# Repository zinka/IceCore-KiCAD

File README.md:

# IceCore-KiCAD
A KiCAD version of IceCore (https://github.com/folknology/IceCore) Lattice FPGA board

**Top View**

**Bottom View**

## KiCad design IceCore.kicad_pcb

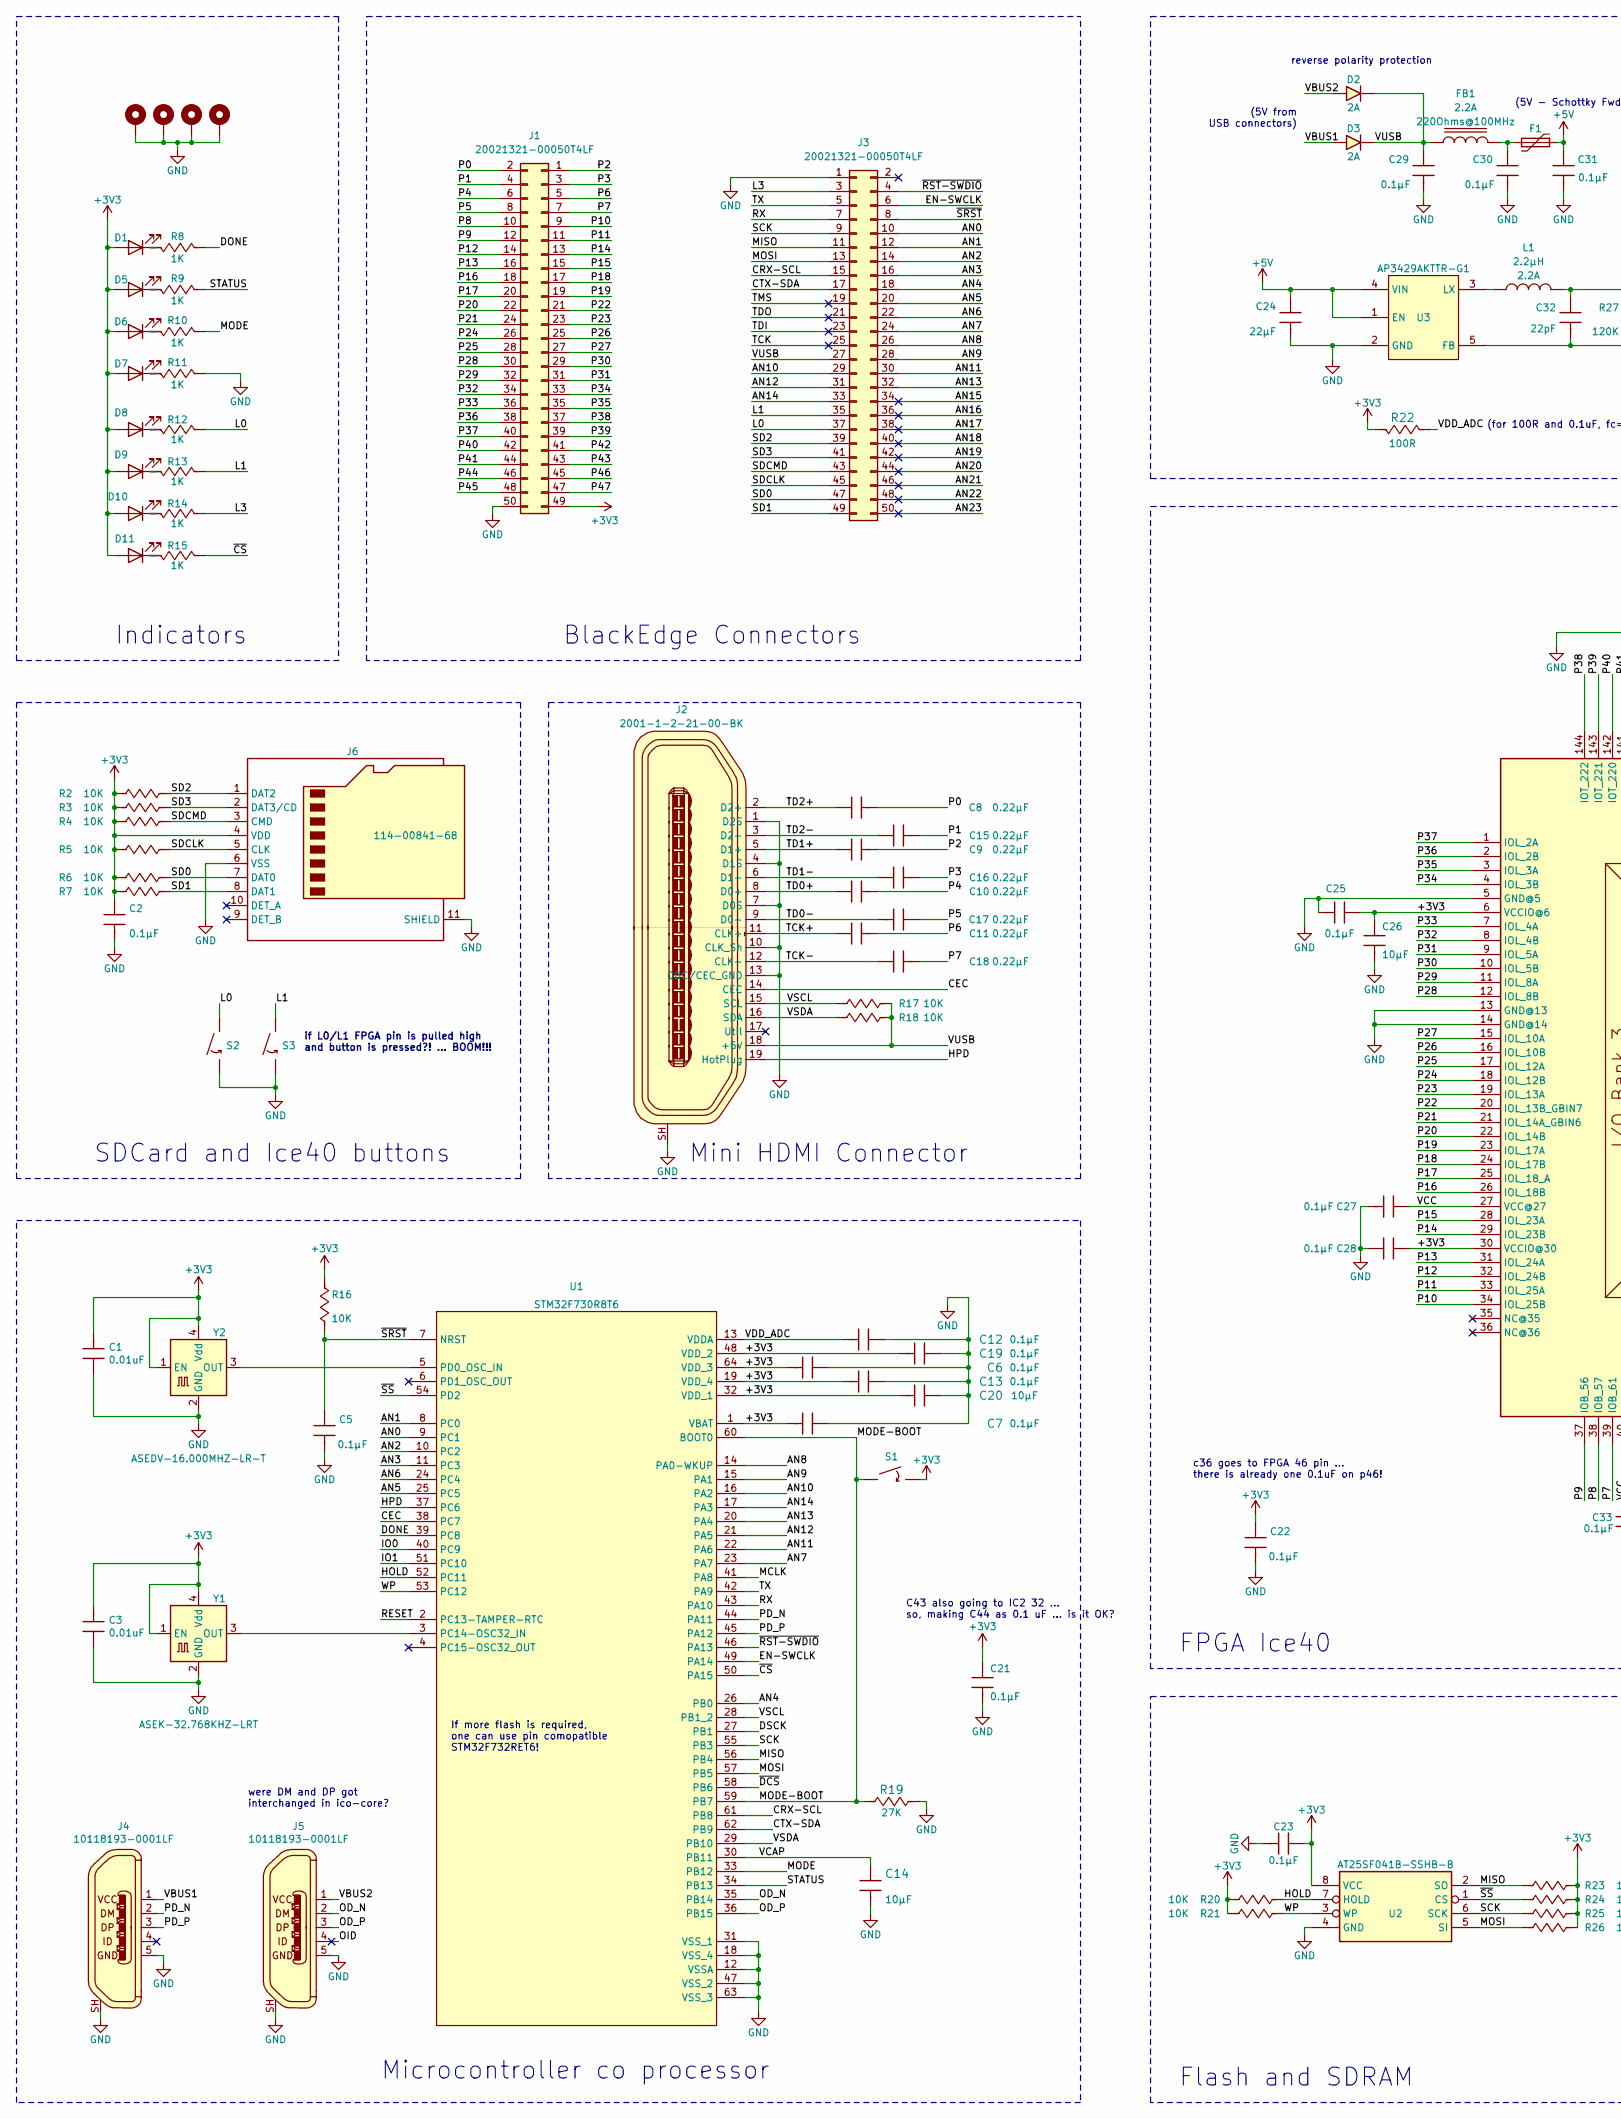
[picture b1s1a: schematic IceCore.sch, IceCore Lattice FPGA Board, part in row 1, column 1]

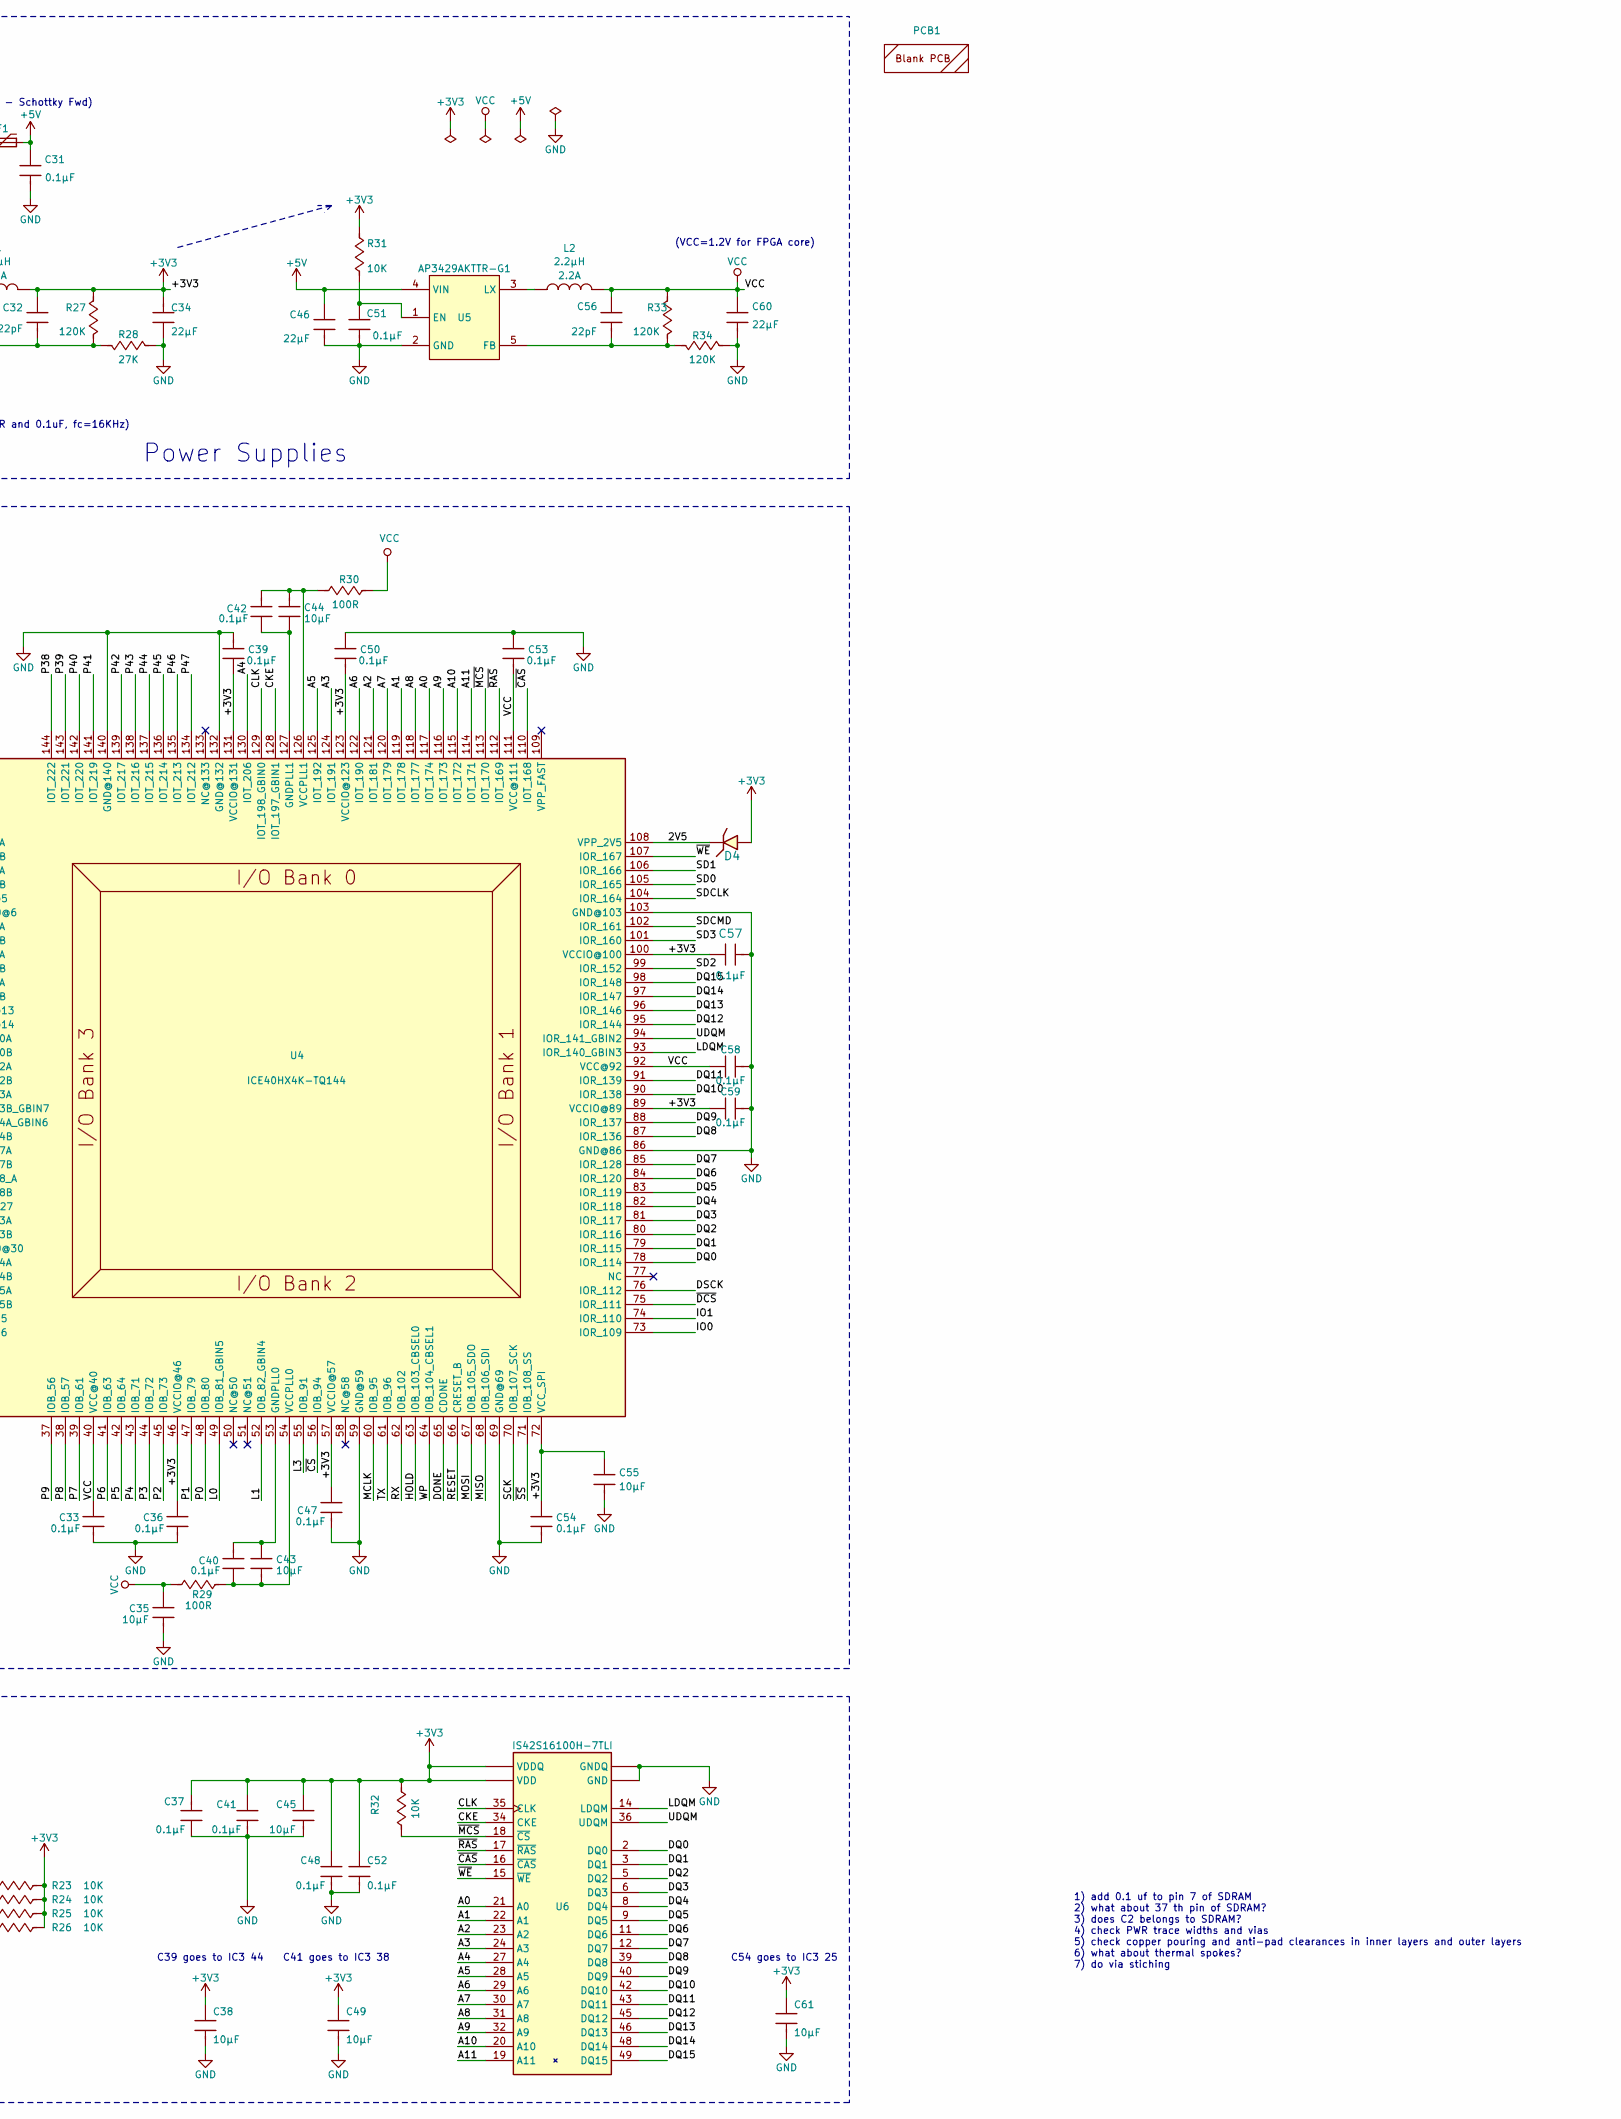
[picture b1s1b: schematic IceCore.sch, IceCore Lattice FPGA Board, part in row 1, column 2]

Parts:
C1, C3: CAP-000017-00; C_0402_1005Metric; Tolerance (%) ±10%; Rated Voltage (Volt) 50V; Manufacturer Part Number GCM155R71H103KA55D
C2, C5, C6, C7, C12, C13, C19, C21, C22, C23, C25, C27, C28, C29, C30, C31, C33, C36, C37, C39, C40, C41, C42, C47, C48, C50, C51, C52, C53, C54, C57, C58, C59: CAP-000004-00; C_0402_1005Metric; Tolerance (%) ±10%; Voltage Rated (Volt) 16V; Manufacturer Part Number GRM155R71C104KA88D
C8, C9, C10, C11, C15, C16, C17, C18: CAP-000182-00; C_0402_1005Metric; Rated Voltage (Volt) 16V; Tolerance (%) ±10%; Manufacturer Part Number GRM155R71C224KA12D
C14, C20, C35, C43, C44, C45: CAP-000178-00; C_0603_1608Metric; Rated Voltage (Volt) 16V; Tolerance (%) ±20%; Manufacturer Part Number CL10X106MO8NRNC
C24, C34, C46, C60: CAP-000164-00; C_0805_2012Metric; Rated Voltage (Volt) 10V; Tolerance (%) ±20%; Manufacturer Part Number GRM21BC81A226ME44L
C26, C38, C49, C55, C61: CAP-000178-00; C_0603_1608Metric; Tolerance (%) ±20%; Rated Voltage (Volt) 16V; Manufacturer Part Number CL10X106MO8NRNC
C32, C56: CAP-000168-00; C_0402_1005Metric; Rated Voltage (Volt) 50V; Tolerance (%) ±5%; Manufacturer Part Number GCM1555C1H220JA16D
D1, D5, D6, D7, D8, D9, D10, D11: DIO-000055-00; LED_0603_1608Metric; Forward Voltage (Volt) 2V; Manufacturer Part Number APT1608EC
D2, D3: DIO-000179-00; D_SOD-123F; Forward Voltage (Volt) 550mV@2A; Rated Voltage (Volt) 40V; Manufacturer Part Number SS24FL
D4: DIO-000186-00; D_SOD-323; Forward Voltage (Volt) 1V@15mA; Rated Voltage (Volt) 70V; Manufacturer Part Number BAS70JFILM
F1: PRO-000190-00; Fuse_1210_3225Metric; Manufacturer Part Number 0ZCH0075AF2E
FB1: IND-000180-00; L_0603_1608Metric; Current Rating (Ampere) 2.2A; Manufacturer Part Number BLM18KG221SN1D
H1, H2, H3, H4: MountingHole_Pad; 2.5MM-HOLE
J1, J3: CON-000177-00; PinSocket_2x25_P1.27mm_Vertical_SMD; Manufacturer Part Number 20021321-00050T4LF
J2: CON-000176-00; HDMI_Mini_Female_2001-1-2-21-00-BK; Manufacturer Part Number 2001-1-2-21-00-BK
J4, J5: CON-000183-00; USB_Micro_B_Female_10118193-0001LF; Manufacturer Part Number 10118193-0001LF
J6: CON-000174-00; AMPHENOL_1140084168; Manufacturer Part Number 114-00841-68
L1, L2: IND-000181-00; L_Taiyo-Yuden_NR-40xx; Current Rating (Ampere) 2.2A; Manufacturer Part Number NRS4018T2R2MDGJ
PCB1: BlankPCB
R2, R3, R4, R5, R6, R7, R16, R17, R18, R20, R21, R23, R24, R25, R26, R31, R32: RES-000076-00; R_0402_1005Metric; Tolerance (%) ±1%; Manufacturer Part Number RC0402FR-1310KL
R8, R9, R10, R11, R12, R13, R14, R15: RES-000092-00; R_0402_1005Metric; Tolerance (%) ±1%; Manufacturer Part Number RC0402FR-071KL
R19, R28: RES-000167-00; R_0402_1005Metric; Tolerance (%) ±1%; Manufacturer Part Number RC0402FR-0727KL
R22, R29, R30: RES-000074-00; R_0402_1005Metric; Tolerance (%) ±1%; Manufacturer Part Number RC0402FR-07100RL
R27, R33, R34: RES-000166-00; R_0402_1005Metric; Tolerance (%) ±1%; Manufacturer Part Number RC0402FR-07120KL
S1, S2, S3: MEC-000189-00; PTS636SL43SMTRLFS; Manufacturer Part Number PTS636 SL43 SMTR LFS
U1: ICS-000169-00; LQFP-64_10x10mm_P0.5mm; Manufacturer Part Number STM32F730R8T6
U2: ICS-000173-00; SOIC-8_3.9x4.9mm_P1.27mm; Manufacturer Part Number AT25SF041B-SSHB-B
U3, U5: PWR-000165-00; TSOT-23-5; Manufacturer Part Number AP3429AKTTR-G1
U4: ICS-000170-00; TQFP-144_20x20mm_P0.5mm; Manufacturer Part Number ICE40HX4K-TQ144
U6: ICS-000172-00; TSOP-2-50; Manufacturer Part Number IS42S16100H-7TLI
Y1: CLK-000184-00; Oscillator_SMD_Abracon_ASE-4Pin_3.2x2.5mm; Manufacturer Part Number ASEK-32.768KHZ-LRT
Y2: CLK-000185-00; Oscillator_SMD_Abracon_ASE-4Pin_3.2x2.5mm; Manufacturer Part Number ASEDV-16.000MHZ-LR-T

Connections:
+3V3: C1.2, C2.1, C3.2, C6.2, C7.2, C13.2, C19.2, C20.2, C21.1, C22.1, C23.1, C25.1, C26.1, C28.2, C32.1, C34.2, C36.1, C37.2, C38.1, C39.1, C41.1, C45.1, C47.1, C48.1, C49.1, C50.2, C52.1, C54.1, C55.1, C57.1, C59.1, C61.1, D1.2 (A), D4.2 (Anode), D5.2 (A), D6.2 (A), D7.2 (A), D8.2 (A), D9.2 (A), D10.2 (A), D11.2 (A), J1.49, J6.4 (VDD), L1.2, R2.2, R3.2, R4.2, R5.2, R6.2, R7.2, R16.2, R20.1, R21.1, R22.1, R23.1, R24.1, R25.1, R26.1, R27.2, R31.1, R32.2, S1.2, U1.1 (VBAT), U1.19 (VDD_4), U1.32 (VDD_1), U1.48 (VDD_2), U1.64 (VDD_3), U2.8 (VCC), U4.6 (VCCIO@6), U4.30 (VCCIO@30), U4.46 (VCCIO@46), U4.57 (VCCIO@57), U4.72 (VCC_SPI), U4.89 (VCCIO@89), U4.100 (VCCIO@100), U4.123 (VCCIO@123), U4.131 (VCCIO@131), U6.1 (VDD), U6.7 (VDDQ), U6.13 (VDDQ), U6.25 (VDD), U6.38 (VDDQ), U6.44 (VDDQ), Y1.1 (EN), Y1.4 (Vdd), Y2.1 (EN), Y2.4 (Vdd)
+5V: C24.1, C31.1, C46.1, F1.1, U3.1 (EN), U3.4 (VIN), U5.4 (VIN)
/2V5: D4.1 (Cathode), U4.108 (VPP_2V5)
/A0: U4.117 (IOT_174), U6.21 (A0)
/A1: U4.119 (IOT_178), U6.22 (A1)
/A2: U4.121 (IOT_181), U6.23 (A2)
/A3: U4.124 (IOT_191), U6.24 (A3)
/A4: U4.130 (IOT_206), U6.27 (A4)
/A5: U4.125 (IOT_192), U6.28 (A5)
/A6: U4.122 (IOT_190), U6.29 (A6)
/A7: U4.120 (IOT_179), U6.30 (A7)
/A8: U4.118 (IOT_177), U6.31 (A8)
/A9: U4.116 (IOT_173), U6.32 (A9)
/A10: U4.115 (IOT_172), U6.20 (A10)
/A11: U4.114 (IOT_171), U6.19 (A11)
/AN0: J3.10, U1.9 (PC1)
/AN1: J3.12, U1.8 (PC0)
/AN2: J3.14, U1.10 (PC2)
/AN3: J3.16, U1.11 (PC3)
/AN4: J3.18, U1.26 (PB0)
/AN5: J3.20, U1.25 (PC5)
/AN6: J3.22, U1.24 (PC4)
/AN7: J3.24, U1.23 (PA7)
/AN8: J3.26, U1.14 (PA0-WKUP)
/AN9: J3.28, U1.15 (PA1)
/AN10: J3.29, U1.16 (PA2)
/AN11: J3.30, U1.22 (PA6)
/AN12: J3.31, U1.21 (PA5)
/AN13: J3.32, U1.20 (PA4)
/AN14: J3.33, U1.17 (PA3)
/AN15: J3.34
/AN16: J3.36
/AN17: J3.38
/AN18: J3.40
/AN19: J3.42
/AN20: J3.44
/AN21: J3.46
/AN22: J3.48
/AN23: J3.50
/CEC: J2.14 (CEC), U1.38 (PC7)
/CKE: U4.128 (IOT_197_GBIN1), U6.34 (CKE)
/CLK: U4.129 (IOT_198_GBIN0), U6.35 (CLK)
/CRX-SCL: J3.15, U1.61 (PB8)
/CTX-SDA: J3.17, U1.62 (PB9)
/DONE: R8.1, U1.39 (PC8), U4.65 (CDONE)
/DQ0: U4.78 (IOR_114), U6.2 (DQ0)
/DQ1: U4.79 (IOR_115), U6.3 (DQ1)
/DQ2: U4.80 (IOR_116), U6.5 (DQ2)
/DQ3: U4.81 (IOR_117), U6.6 (DQ3)
/DQ4: U4.82 (IOR_118), U6.8 (DQ4)
/DQ5: U4.83 (IOR_119), U6.9 (DQ5)
/DQ6: U4.84 (IOR_120), U6.11 (DQ6)
/DQ7: U4.85 (IOR_128), U6.12 (DQ7)
/DQ8: U4.87 (IOR_136), U6.39 (DQ8)
/DQ9: U4.88 (IOR_137), U6.40 (DQ9)
/DQ10: U4.90 (IOR_138), U6.42 (DQ10)
/DQ11: U4.91 (IOR_139), U6.43 (DQ11)
/DQ12: U4.95 (IOR_144), U6.45 (DQ12)
/DQ13: U4.96 (IOR_146), U6.46 (DQ13)
/DQ14: U4.97 (IOR_147), U6.48 (DQ14)
/DQ15: U4.98 (IOR_148), U6.49 (DQ15)
/DSCK: U1.27 (PB1), U4.76 (IOR_112)
/EN-SWCLK: J3.6, U1.49 (PA14)
/HOLD: R20.2, U1.52 (PC11), U2.7 (HOLD), U4.63 (IOB_103_CBSEL0)
/HPD: J2.19 (HotPlug), U1.37 (PC6)
/IO0: U1.40 (PC9), U4.73 (IOR_109)
/IO1: U1.51 (PC10), U4.74 (IOR_110)
/L0: J3.37, R12.2, S2.1, U4.49 (IOB_81_GBIN5)
/L1: J3.35, R13.2, S3.1, U4.52 (IOB_82_GBIN4)
/L3: J3.3, R14.2, U4.55 (IOB_91)
/LDQM: U4.93 (IOR_140_GBIN3), U6.14 (LDQM)
/MCLK: U1.41 (PA8), U4.60 (IOB_95)
/MISO: J3.11, R23.2, U1.56 (PB4), U2.2 (SO), U4.68 (IOB_106_SDI)
/MODE: R10.1, U1.33 (PB12)
/MODE-BOOT: R19.1, S1.1, U1.59 (PB7), U1.60 (BOOT0)
/MOSI: J3.13, R26.2, U1.57 (PB5), U2.5 (SI), U4.67 (IOB_105_SDO)
/OD_N: J5.2, U1.35 (PB14)
/OD_P: J5.3, U1.36 (PB15)
/OID: J5.4
/P0: C8.2, J1.2, U4.48 (IOB_80)
/P1: C15.2, J1.4, U4.47 (IOB_79)
/P2: C9.2, J1.1, U4.45 (IOB_73)
/P3: C16.2, J1.3, U4.44 (IOB_72)
/P4: C10.2, J1.6, U4.43 (IOB_71)
/P5: C17.1, J1.8, U4.42 (IOB_64)
/P6: C11.2, J1.5, U4.41 (IOB_63)
/P7: C18.2, J1.7, U4.39 (IOB_61)
/P8: J1.10, U4.38 (IOB_57)
/P9: J1.12, U4.37 (IOB_56)
/P10: J1.9, U4.34 (IOL_25B)
/P11: J1.11, U4.33 (IOL_25A)
/P12: J1.14, U4.32 (IOL_24B)
/P13: J1.16, U4.31 (IOL_24A)
/P14: J1.13, U4.29 (IOL_23B)
/P15: J1.15, U4.28 (IOL_23A)
/P16: J1.18, U4.26 (IOL_18B)
/P17: J1.20, U4.25 (IOL_18_A)
/P18: J1.17, U4.24 (IOL_17B)
/P19: J1.19, U4.23 (IOL_17A)
/P20: J1.22, U4.22 (IOL_14B)
/P21: J1.24, U4.21 (IOL_14A_GBIN6)
/P22: J1.21, U4.20 (IOL_13B_GBIN7)
/P23: J1.23, U4.19 (IOL_13A)
/P24: J1.26, U4.18 (IOL_12B)
/P25: J1.28, U4.17 (IOL_12A)
/P26: J1.25, U4.16 (IOL_10B)
/P27: J1.27, U4.15 (IOL_10A)
/P28: J1.30, U4.12 (IOL_8B)
/P29: J1.32, U4.11 (IOL_8A)
/P30: J1.29, U4.10 (IOL_5B)
/P31: J1.31, U4.9 (IOL_5A)
/P32: J1.34, U4.8 (IOL_4B)
/P33: J1.36, U4.7 (IOL_4A)
/P34: J1.33, U4.4 (IOL_3B)
/P35: J1.35, U4.3 (IOL_3A)
/P36: J1.38, U4.2 (IOL_2B)
/P37: J1.40, U4.1 (IOL_2A)
/P38: J1.37, U4.144 (IOT_222)
/P39: J1.39, U4.143 (IOT_221)
/P40: J1.42, U4.142 (IOT_220)
/P41: J1.44, U4.141 (IOT_219)
/P42: J1.41, U4.139 (IOT_217)
/P43: J1.43, U4.138 (IOT_216)
/P44: J1.46, U4.137 (IOT_215)
/P45: J1.48, U4.136 (IOT_214)
/P46: J1.45, U4.135 (IOT_213)
/P47: J1.47, U4.134 (IOT_212)
/PD_N: J4.2, U1.44 (PA11)
/PD_P: J4.3, U1.45 (PA12)
/RESET: U1.2 (PC13-TAMPER-RTC), U4.66 (CRESET_B)
/RX: J3.7, U1.43 (PA10), U4.62 (IOB_102)
/SCK: J3.9, R25.2, U1.55 (PB3), U2.6 (SCK), U4.70 (IOB_107_SCK)
/SD0: J3.47, J6.7 (DAT0), R6.1, U4.105 (IOR_165)
/SD1: J3.49, J6.8 (DAT1), R7.1, U4.106 (IOR_166)
/SD2: J3.39, J6.1 (DAT2), R2.1, U4.99 (IOR_152)
/SD3: J3.41, J6.2 (DAT3/CD), R3.1, U4.101 (IOR_160)
/SDCLK: J3.45, J6.5 (CLK), R5.1, U4.104 (IOR_164)
/SDCMD: J3.43, J6.3 (CMD), R4.1, U4.102 (IOR_161)
/STATUS: R9.1, U1.34 (PB13)
/TCK: J3.25
/TCK+: C11.1, J2.11 (CLK+)
/TCK-: C18.1, J2.12 (CLK-)
/TD0+: C10.1, J2.8 (D0+)
/TD0-: C17.2, J2.9 (D0-)
/TD1+: C9.1, J2.5 (D1+)
/TD1-: C16.1, J2.6 (D1-)
/TD2+: C8.1, J2.2 (D2+)
/TD2-: C15.1, J2.3 (D2-)
/TDI: J3.23
/TDO: J3.21
/TMS: J3.19
/TX: J3.5, U1.42 (PA9), U4.61 (IOB_96)
/UDQM: U4.94 (IOR_141_GBIN2), U6.36 (UDQM)
/VBUS1: D3.2 (Anode), J4.1
/VBUS2: D2.2 (Anode), J5.1
/VCAP: C14.1, U1.30 (PB11)
/VDD_ADC: C12.2, R22.2, U1.13 (VDDA)
/VSCL: J2.15 (SCL), R17.2, U1.28 (PB1_2)
/VSDA: J2.16 (SDA), R18.2, U1.29 (PB10)
/VUSB: C29.1, D2.1 (Cathode), D3.1 (Cathode), FB1.1, J2.18 (+5V), J3.27, R17.1, R18.1
/WP: R21.2, U1.53 (PC12), U2.3 (WP), U4.64 (IOB_104_CBSEL1)
/~CAS: U4.110 (IOT_168), U6.16 (~CAS)
/~CS: R15.2, U1.50 (PA15), U4.56 (IOB_94)
/~DCS: U1.58 (PB6), U4.75 (IOR_111)
/~MCS: R32.1, U4.113 (IOT_170), U6.18 (~CS)
/~RAS: U4.112 (IOT_169), U6.17 (~RAS)
/~RST-SWDIO: J3.4, U1.46 (PA13)
/~SRST: C5.1, J3.8, R16.1, U1.7 (NRST)
/~SS: R24.2, U1.54 (PD2), U2.1 (CS), U4.71 (IOB_108_SS)
/~WE: U4.107 (IOR_167), U6.15 (~WE)
GND: C1.1, C2.2, C3.1, C5.2, C6.1, C7.1, C12.1, C13.1, C14.2, C19.1, C20.1, C21.2, C22.2, C23.2, C24.2, C25.2, C26.2, C27.2, C28.1, C29.2, C30.2, C31.2, C33.2, C34.1, C35.2, C36.2, C37.1, C38.2, C39.2, C41.2, C45.2, C46.2, C47.2, C48.2, C49.2, C50.1, C51.2, C52.2, C53.1, C54.2, C55.2, C57.2, C58.2, C59.2, C60.2, C61.2, H1.1, H2.1, H3.1, H4.1, J1.50, J2.1 (D2S), J2.4 (D1S), J2.7 (D0S), J2.10 (CLK_Sh), J2.13 (DDC/CEC_GND), J2.SH, J3.1, J4.5, J4.SH, J5.5, J5.SH, J6.6 (VSS), J6.11 (SHIELD), R11.1, R19.2, R28.2, R34.2, S2.2, S3.2, U1.12 (VSSA), U1.18 (VSS_4), U1.31 (VSS_1), U1.47 (VSS_2), U1.63 (VSS_3), U2.4 (GND), U3.2 (GND), U4.5 (GND@5), U4.13 (GND@13), U4.14 (GND@14), U4.59 (GND@59), U4.69 (GND@69), U4.86 (GND@86), U4.103 (GND@103), U4.132 (GND@132), U4.140 (GND@140), U5.2 (GND), U6.4 (GNDQ), U6.10 (GNDQ), U6.26 (GND), U6.41 (GNDQ), U6.47 (GNDQ), U6.50 (GND), Y1.2 (GND), Y2.2 (GND)
unnamed: C30.1, F1.2, FB1.2
unnamed: C32.2, R27.1, R28.1, U3.5 (FB)
unnamed: C40.1, C43.2, R29.1, U4.54 (VCCPLL0)
unnamed: C40.2, C43.1, U4.53 (GNDPLL0)
unnamed: C42.1, C44.1, U4.127 (GNDPLL1)
unnamed: C42.2, C44.2, R30.2, U4.126 (VCCPLL1)
unnamed: C51.1, R31.2, U5.1 (EN)
unnamed: C56.2, R33.1, R34.1, U5.5 (FB)
unnamed: D1.1 (K), R8.2
unnamed: D5.1 (K), R9.2
unnamed: D6.1 (K), R10.2
unnamed: D7.1 (K), R11.2
unnamed: D8.1 (K), R12.1
unnamed: D9.1 (K), R13.1
unnamed: D10.1 (K), R14.1
unnamed: D11.1 (K), R15.1
unnamed: L1.1, U3.3 (LX)
unnamed: L2.1, U5.3 (LX)
unnamed: U1.3 (PC14-OSC32_IN), Y1.3 (OUT)
unnamed: U1.5 (PD0_OSC_IN), Y2.3 (OUT)
VCC: C27.1, C33.1, C35.1, C53.2, C56.1, C58.1, C60.1, L2.2, R29.2, R30.1, R33.2, U4.27 (VCC@27), U4.40 (VCC@40), U4.92 (VCC@92), U4.111 (VCC@111)

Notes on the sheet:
BlackEdge Connectors
Mini HDMI Connector
FPGA Ice40
Flash and SDRAM
Microcontroller co processor
SDCard and Ice40 buttons
Indicators
Power Supplies
C39 goes to IC3 44
C43 also going to IC2 32 ... so, making C44 as 0.1 uF ... is it OK?
c36 goes to FPGA 46 pin ... there is already one 0.1uF on p46!
C41 goes to IC3 38
C54 goes to IC3 25
reverse polarity protection
(5V from USB connectors)
(5V - Schottky Fwd)
(VCC=1.2V for FPGA core)
(for 100R and 0.1uF, fc=16KHz)
if L0/L1 FPGA pin is pulled high and button is pressed?! ... BOOM!!!
If more flash is required, one can use pin comopatible STM32F732RET6!
were DM and DP got interchanged in ico-core?
1) add 0.1 uf to pin 7 of SDRAM 2) what about 37 th pin of SDRAM? 3) does C2 belongs to SDRAM? 4) check PWR trace widths and vias 5) check copper pouring and anti-pad clearances in inner layers and outer layers 6) what about thermal spokes? 7) do via stiching

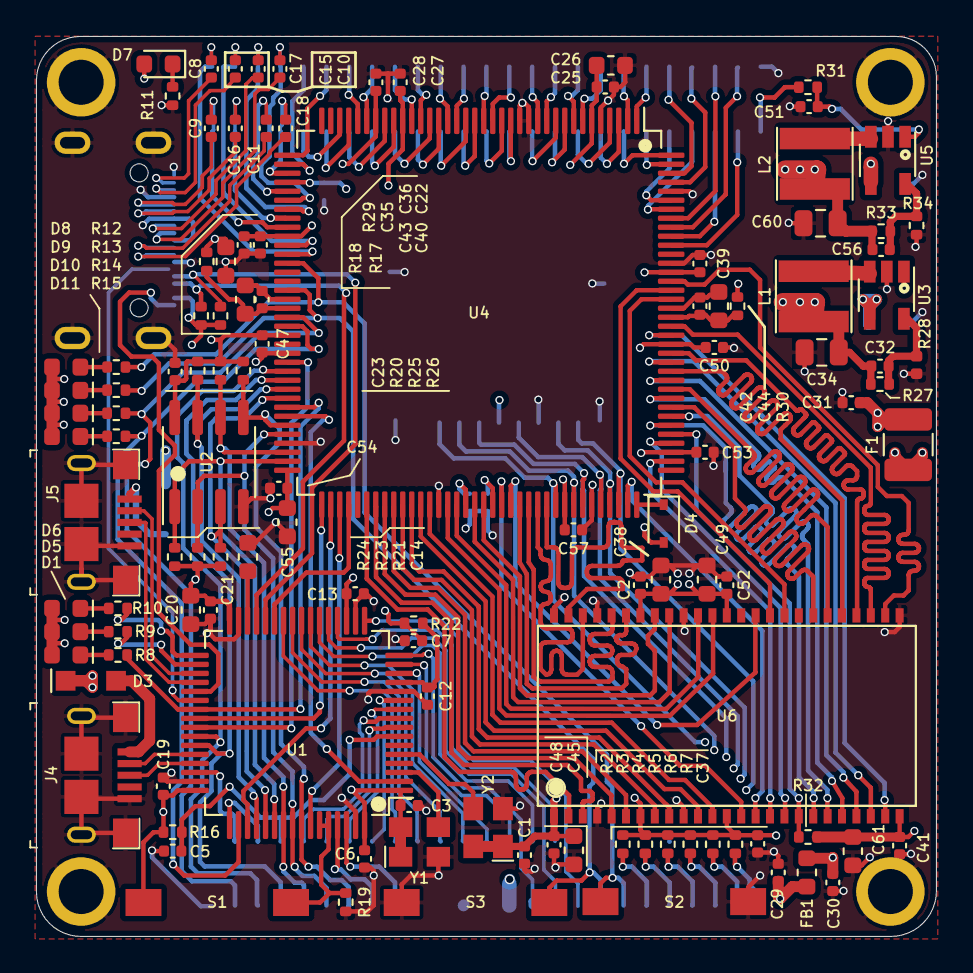
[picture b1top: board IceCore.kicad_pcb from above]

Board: 4 copper layers, 50.0 x 50.0 mm, 129 parts (0 on the bottom side), 178 nets.
